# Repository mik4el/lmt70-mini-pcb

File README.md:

# lmt70-mini-pcb
A miniature pcb for the lmt70 to be mounted on a cable for submersed measurements.

# Testing version 1 of PCB
It works! Nothing majorly wrong with this pcb except that it is very small. It was easy to cut away the excess parts so this is a decent method for my uses. What really didn't work well was the hole size for the connecting parts. The holes need to be about twice the size to work well for wire sizes that are easy to handle.

Assembled pcb:

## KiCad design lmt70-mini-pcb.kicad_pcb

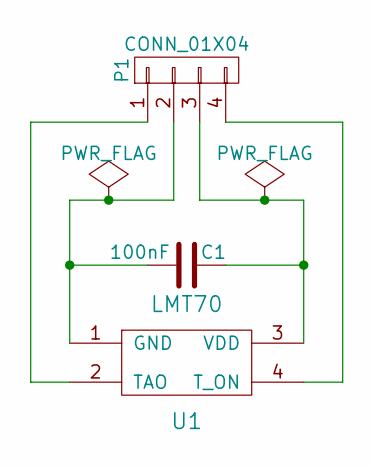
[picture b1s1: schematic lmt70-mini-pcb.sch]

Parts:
C1: 100nF; C_0603
P1: CONN_01X04; Wire_1x04_mini
U1: LMT70

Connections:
unnamed: C1.1, P1.3, U1.3 (VDD)
unnamed: C1.2, P1.2, U1.1 (GND)
unnamed: P1.1, U1.2 (TAO)
unnamed: P1.4, U1.4 (T_ON)

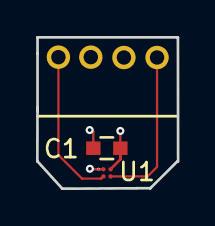
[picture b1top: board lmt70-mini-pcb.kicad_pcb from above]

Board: 4 copper layers, 7.8 x 8.4 mm, 3 parts (0 on the bottom side), 4 nets.

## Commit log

2017-03-31 ordered oshpark pcb v1
2017-04-10 ordered stencil
2018-05-23 Assembled pcb
2018-06-01 updated pcb to fit bigger cables
2018-06-04 termo buffer from cable
2018-08-16 PCB changed for manufacturing with JLCPCB
2018-08-24 PCB sent to manufaturing
